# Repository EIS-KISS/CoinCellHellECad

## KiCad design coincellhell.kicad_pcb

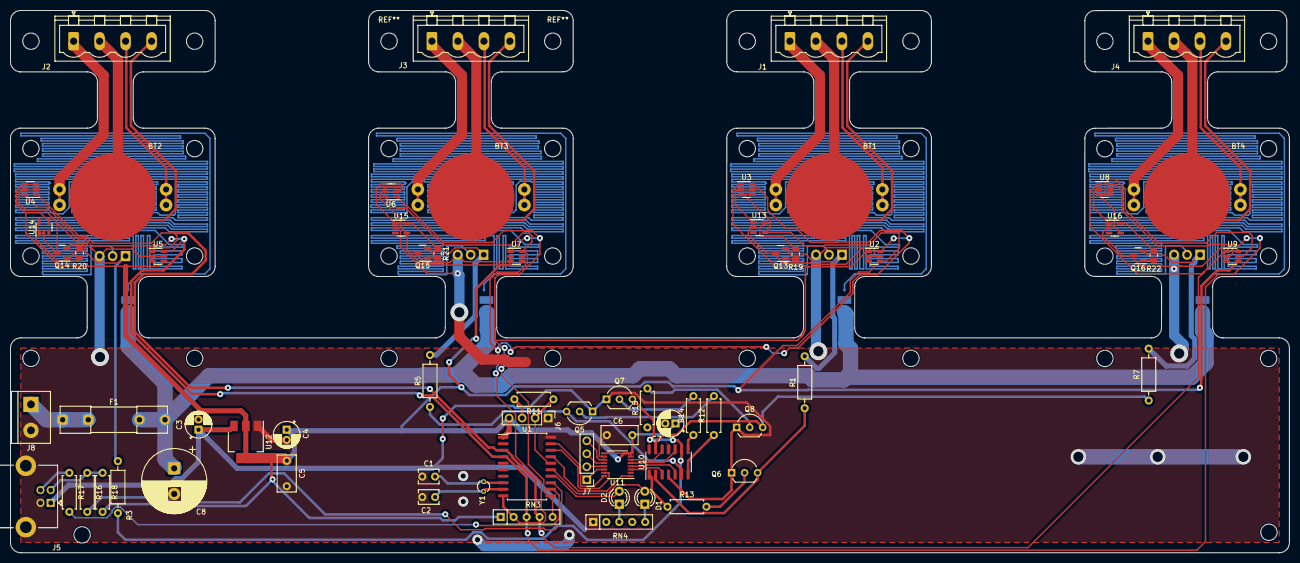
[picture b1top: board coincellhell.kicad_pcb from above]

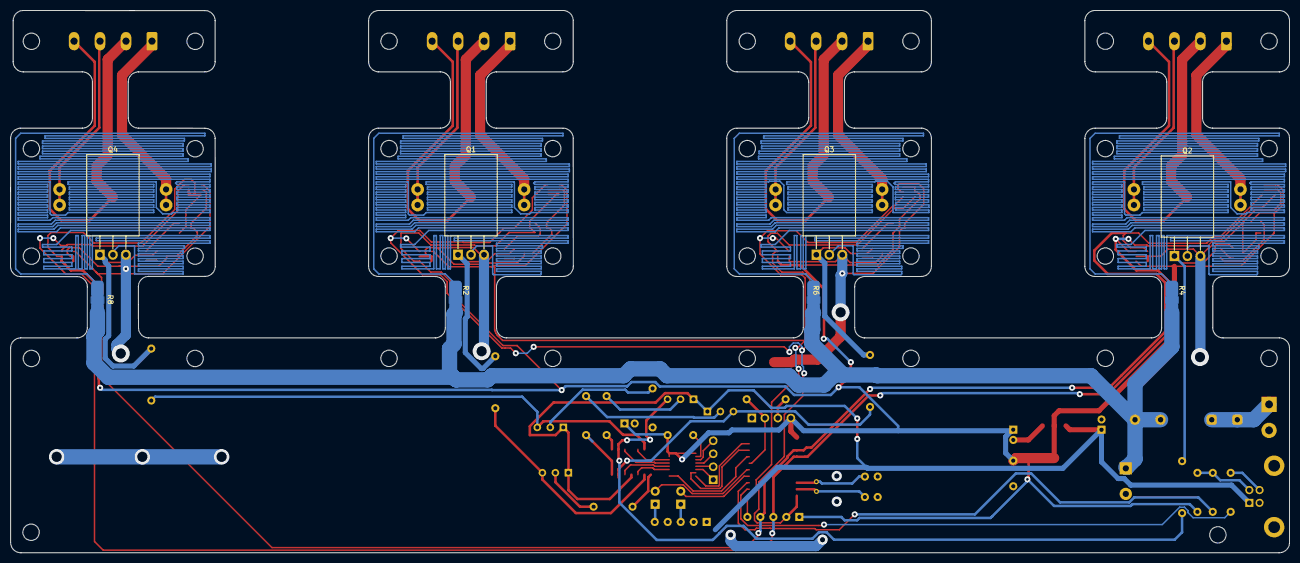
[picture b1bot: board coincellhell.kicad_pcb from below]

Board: 2 copper layers, 250.0 x 106.0 mm, 74 parts (8 on the bottom side), 68 nets.

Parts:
BT1, BT2, BT3, BT4: Battery_Cell; CR2032Holder
C1, C2: 6p; C_Disc_D3.8mm_W2.6mm_P2.50mm
C3, C4, C7: 100u; CP_Radial_D5.0mm_P2.00mm
C5, C6: 10n; C_Rect_L7.0mm_W3.5mm_P5.00mm
C8: 470u 50v; CP_Radial_D12.5mm_P5.00mm
D1, D2: LED; LED_D3.0mm
F1: Fuse; Fuseholder_Clip-5x20mm_Littelfuse_111_Inline_P20.00x5.00mm_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
J1, J2, J3, J4: Conn_01x04_Pin; PhoenixContact_MSTBVA_2,5_4-G-5,08_1x04_P5.08mm_Vertical
J5: USB_B; USB_B_Lumberg_2411_02_Horizontal
J6, J7: Conn_01x04_Pin; PinHeader_1x04_P2.54mm_Vertical
J8: Conn_01x02_Pin; TerminalBlock_bornier-2_P5.08mm
Q1, Q2, Q3, Q4: TIP41; TO-220-3_Horizontal_TabDown
Q5, Q6, Q7, Q8: BC337; TO-92_Inline_Wide
Q13, Q14, Q15, Q16: BC807; SOT-23
R1, R3, R5, R7: 50R 0.5W; R_Axial_DIN0207_L6.3mm_D2.5mm_P10.16mm_Horizontal
R2, R4, R6, R8: RPCB; PCBResistor
R11: 1K; R_Axial_DIN0207_L6.3mm_D2.5mm_P7.62mm_Horizontal
R12, R13, R14, R15: 100R; R_Axial_DIN0207_L6.3mm_D2.5mm_P7.62mm_Horizontal
R16, R17: 68R; R_Axial_DIN0207_L6.3mm_D2.5mm_P7.62mm_Horizontal
R18: 1.5K; R_Axial_DIN0207_L6.3mm_D2.5mm_P7.62mm_Horizontal
R19, R20, R21, R22: 1K; R_0805_2012Metric
RN3: R_Network04; R_Array_SIP5
RN4: 120R; R_Array_SIP5
U1: ATtiny3226-S; SOIC-20W_7.5x12.8mm_P1.27mm
U2, U3, U4, U5, U6, U7, U8, U9: TMP100; SOT-23-6
U10: TL084; SOIC-14_3.9x8.7mm_P1.27mm
U11: SSOP-16_3.9x4.9mm_P0.635mm
U12: LM1117MP-3.3; SOT-223-3_TabPin2
U13, U14, U15, U16: LM27; SOT-23-5
Y1: 32.768kHz; Crystal_Round_D2.0mm_Vertical

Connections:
+3.3V: C4.1, C5.1, C6.1, C7.1, J6.4, R18.2, RN3.1 (common), U1.1 (VCC), U2.4 (V+), U3.3 (ADD1), U3.4 (V+), U4.3 (ADD1), U4.4 (V+), U5.4 (V+), U6.3 (ADD1), U6.4 (V+), U6.5 (ADD0), U7.4 (V+), U7.5 (ADD0), U8.3 (ADD1), U8.4 (V+), U8.5 (ADD0), U9.4 (V+), U9.5 (ADD0), U11.7 (Vcc), U11.8 (V_REF1), U11.9 (V_REF2), U12.2 (VO), U13.4 (VCC), U14.4 (VCC), U15.4 (VCC), U16.4 (VCC)
+5V: C3.1, J5.1 (VBUS), Q5.1 (C), Q6.1 (C), Q7.1 (C), Q8.1 (C), U10.4 (V+), U12.3 (VI)
+24V: C8.1, F1.2, R2.2, R4.2, R6.2, R8.2
/Heater1/HEATER: Q7.3 (E), R3.1, U10.9 (-)
/Heater2/HEATER: Q5.3 (E), R5.1, U10.6 (-)
/Heater3/HEATER: Q8.3 (E), R7.1, U10.13 (-)
/Heater/HEATER: Q6.3 (E), R1.1, U10.2 (-)
GND: C1.1, C2.1, C3.2, C4.2, C5.2, C6.2, C7.2, C8.2, J5.4 (GND), J5.5 (Shield), J6.1, J8.2, Q1.3 (E), Q2.3 (E), Q3.3 (E), Q4.3 (E), Q13.3 (C), Q14.3 (C), Q15.3 (C), Q16.3 (C), RN4.1 (common), U1.20 (GND), U2.2 (GND), U2.3 (ADD1), U2.5 (ADD0), U3.2 (GND), U3.5 (ADD0), U4.2 (GND), U4.5 (ADD0), U5.2 (GND), U5.3 (ADD1), U5.5 (ADD0), U6.2 (GND), U7.2 (GND), U7.3 (ADD1), U8.2 (GND), U9.2 (GND), U9.3 (ADD1), U10.11 (V-), U11.10 (GND), U12.1 (GND), U13.1 (HYST), U13.2 (GND), U14.1 (HYST), U14.2 (GND), U15.1 (HYST), U15.2 (GND), U16.1 (HYST), U16.2 (GND)
unnamed: BT1.1 (+), J1.2, J1.4
unnamed: BT1.2 (-), J1.1, J1.3
unnamed: BT2.1 (+), J2.2, J2.4
unnamed: BT2.2 (-), J2.1, J2.3
unnamed: BT3.1 (+), J3.2, J3.4
unnamed: BT3.2 (-), J3.1, J3.3
unnamed: BT4.1 (+), J4.2, J4.4
unnamed: BT4.2 (-), J4.1, J4.3
unnamed: D1.2 (A), U1.15 (PC3)
unnamed: D1.1 (K), RN4.5 (R4)
unnamed: D2.2 (A), U1.14 (PC2)
unnamed: D2.1 (K), RN4.3 (R2)
unnamed: J5.3 (D+), R17.1
unnamed: J5.2 (D-), R16.1, R18.1
unnamed: J6.2, R11.1, U1.16 (~RESET/PA0)
unnamed: J6.3, R11.2
unnamed: J7.1, U11.14 (V_e)
unnamed: J7.2, U11.13 (V_f)
unnamed: J7.3, U11.12 (V_g)
unnamed: J7.4, U11.11 (V_h)
unnamed: F1.1, J8.1
unnamed: Q1.1 (B), Q13.2 (E), R1.2
unnamed: Q1.2 (C), R2.1
unnamed: Q2.2 (C), R4.1
unnamed: Q3.2 (C), R6.1
unnamed: Q4.2 (C), R8.1
unnamed: Q5.2 (B), R12.2
unnamed: Q6.2 (B), R13.2
unnamed: Q7.2 (B), R14.2
unnamed: Q8.2 (B), R15.2
unnamed: Q13.1 (B), R19.2
unnamed: Q14.1 (B), R20.2
unnamed: Q2.1 (B), Q14.2 (E), R3.2
unnamed: Q15.1 (B), R21.2
unnamed: Q3.1 (B), Q15.2 (E), R5.2
unnamed: Q16.1 (B), R22.2
unnamed: Q4.1 (B), Q16.2 (E), R7.2
unnamed: R12.1, U10.7
unnamed: R13.1, U10.1
unnamed: R14.1, U10.8
unnamed: R15.1, U10.14
unnamed: U1.17 (PA1), U11.1 (D_in)
unnamed: U1.18 (PA2), U11.15 (SYNC)
unnamed: U1.19 (PA3), U11.16 (SCLK)
unnamed: C2.2, U1.9 (PB2), Y1.1
unnamed: C1.2, U1.8 (PB3), Y1.2
unnamed: R17.2, U1.12 (PC0)
unnamed: R16.2, U1.13 (PC1)
unnamed: U10.3 (+), U11.3 (V_a)
unnamed: U10.5 (+), U11.4 (V_b)
unnamed: U10.10 (+), U11.5 (V_c)
unnamed: U10.12 (+), U11.6 (V_d)
unnamed: R19.1, U13.5 (OS)
unnamed: R20.1, U14.5 (OS)
unnamed: R21.1, U15.5 (OS)
unnamed: R22.1, U16.5 (OS)
SCL_A: RN3.5 (R4), U1.11 (PB0), U2.1 (SCL), U3.1 (SCL), U6.1 (SCL), U7.1 (SCL)
SCL_B: RN3.4 (R3), U1.3 (PA5), U4.1 (SCL), U5.1 (SCL), U8.1 (SCL), U9.1 (SCL)
SDA_A: RN3.2 (R1), U1.10 (PB1), U2.6 (SDA), U3.6 (SDA), U6.6 (SDA), U7.6 (SDA)
SDA_B: RN3.3 (R2), U1.4 (PA6), U4.6 (SDA), U5.6 (SDA), U8.6 (SDA), U9.6 (SDA)

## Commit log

2023-07-17 inital commit
2023-08-15 rev 1.0
